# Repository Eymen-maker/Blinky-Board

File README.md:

# Blinky-Board

A blinky board that i made with free-form wiring (aka no pcb, only wire ), but it still has a pcb file to be my reference point.
Small note: pcb has 10 leds but real life build only has 5 as hand wiring 10 leds that close would have been hell.

(there is zero short circuits, i also have no idea how)

[blinky board BOM - Sayfa1.csv](https://github.com/user-attachments/files/30831607/blinky.board.BOM.-.Sayfa1.csv)
Names," links (these are all bought physically, from onur çarşısı / izmir)",Notes

555 timer,https://www.robotistan.com/ne555-dip8,

cd4017,https://robotistanpro.com/lingxingic-cd40175bmlx,

1k ohm resistor,https://www.lcsc.com/product-detail/C2979794.html?spm=wm.fly.bg.7.stp___wm.fly.lb.6.ml&lcsc_vid=Q1ZWUgUDEwUMBgZXRQdcA1ACElBeVFVQQgBZVwZXE1cxVlNeRFJaVldeQFdeUzsOAxUeFF5JWBYZEEoBGA4JCwFIFA4DSA%3D%3D, 

470 ohm resistor,https://www.lcsc.com/product-detail/C1374787.html?spm=wm.fly.bg.13.stp___wm.fly.lb.6.ml&lcsc_vid=Q1ZWUgUDEwUMBgZXRQdcA1ACElBeVFVQQgBZVwZXE1cxVlNeRFJaVldeQFdeUzsOAxUeFF5JWBYZEEoBGA4JCwFIFA4DSA%3D%3D, 

1 uF electrolytic capacitor,https://www.lcsc.com/product-detail/C2927584.html?spm=wm.fly.bg.1.stp___wm.fly.tp.1.ml&lcsc_vid=Q1ZWUgUDEwUMBgZXRQdcA1ACElBeVFVQQgBZVwZXE1cxVlNeRFJaVldeQFdeUzsOAxUeFF5JWBYZEEoBGA4JCwFIFA4DSA%3D%3D, 

0.01 uF capacitor,https://www.lcsc.com/product-detail/C2299493.html?spm=wm.fly.bg.0.xh___wm.fly.tp.3.ml&lcsc_vid=Q1ZWUgUDEwUMBgZXRQdcA1ACElBeVFVQQgBZVwZXE1cxVlNeRFJaVldeQFdeUzsOAxUeFF5JWBYZEEoBGA4JCwFIFA4DSA%3D%3D, 

50k varible resistor,https://www.lcsc.com/product-detail/C5848785.html?spm=wm.fly.bg.3.stp___wm.fly.tp.1.ml&lcsc_vid=Q1ZWUgUDEwUMBgZXRQdcA1ACElBeVFVQQgBZVwZXE1cxVlNeRFJaVldeQFdeUzsOAxUeFF5JWBYZEEoBGA4JCwFIFA4DSA%3D%3D,not the same one but any 50 k ohm vareable resistor woud do

10 leds,literally anywhere,was 20x1 i just cut it

2 male socket pieces,literally anywhere,

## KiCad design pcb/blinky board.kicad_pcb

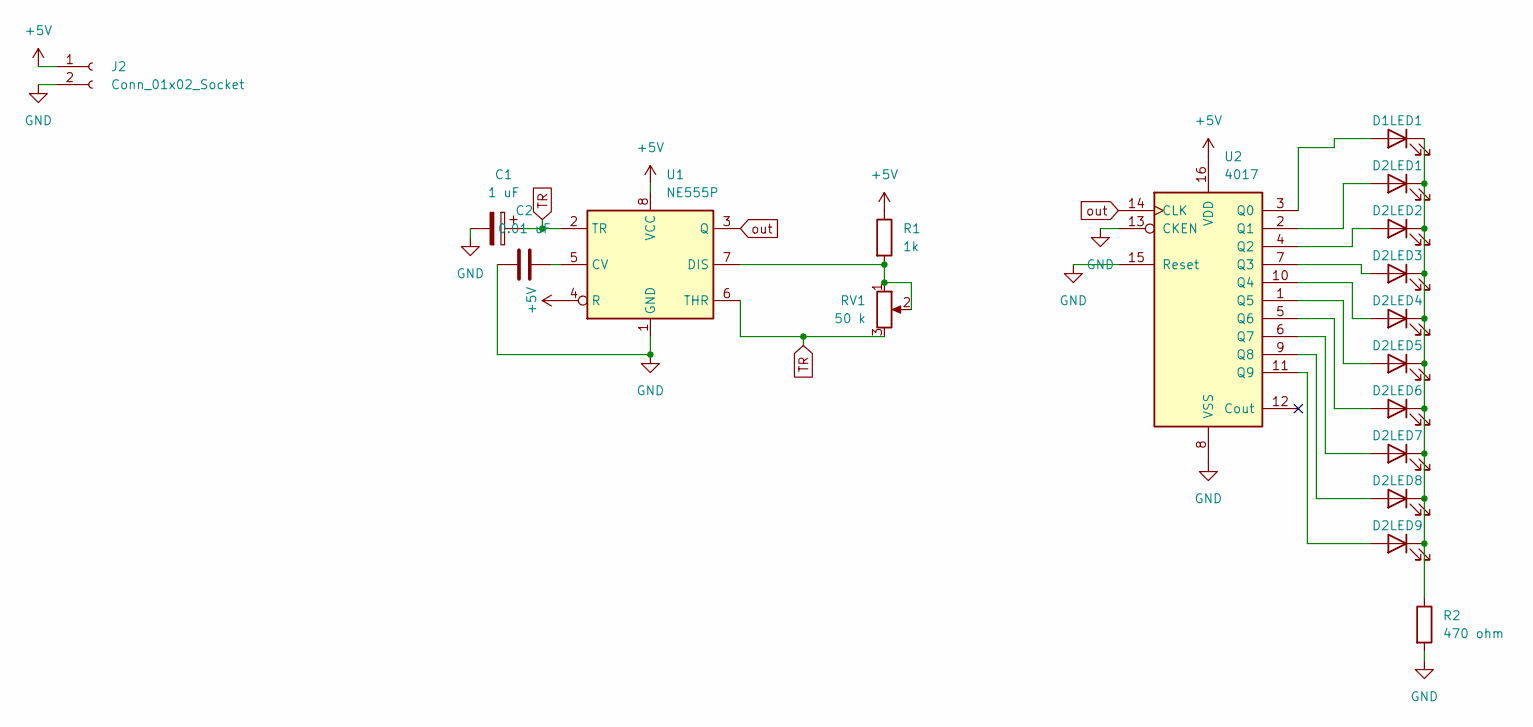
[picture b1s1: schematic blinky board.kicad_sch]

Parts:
C1: 1 uF; CP_Radial_D5.0mm_P2.00mm
C2: 0.01 uF; C_Disc_D7.5mm_W2.5mm_P5.00mm
D1LED1, D2LED1, D2LED2, D2LED3, D2LED4, D2LED5, D2LED6, D2LED7, D2LED8, D2LED9: LED_D3.0mm
J2: Conn_01x02_Socket; PinHeader_1x02_P2.54mm_Vertical
R1: 1k; R_Axial_DIN0207_L6.3mm_D2.5mm_P7.62mm_Horizontal
R2: 470 ohm; R_Axial_DIN0207_L6.3mm_D2.5mm_P7.62mm_Horizontal
RV1: 50 k; Potentiometer_Vishay_T93YA_Vertical
U1: NE555P; DIP-8_W7.62mm
U2: 4017; N16

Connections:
+5V: J2.1, R1.1, U1.4 (R), U1.8 (VCC), U2.16 (VDD)
GND: C1.2, C2.2, J2.2, R2.2, U1.1 (GND), U2.8 (VSS), U2.13 (CKEN), U2.15 (Reset)
unnamed: D1LED1.2 (A), U2.3 (Q0)
unnamed: D1LED1.1 (K), D2LED1.1 (K), D2LED2.1 (K), D2LED3.1 (K), D2LED4.1 (K), D2LED5.1 (K), D2LED6.1 (K), D2LED7.1 (K), D2LED8.1 (K), D2LED9.1 (K), R2.1
unnamed: D2LED1.2 (A), U2.2 (Q1)
unnamed: D2LED2.2 (A), U2.4 (Q2)
unnamed: D2LED3.2 (A), U2.7 (Q3)
unnamed: D2LED4.2 (A), U2.10 (Q4)
unnamed: D2LED5.2 (A), U2.1 (Q5)
unnamed: D2LED6.2 (A), U2.5 (Q6)
unnamed: D2LED7.2 (A), U2.6 (Q7)
unnamed: D2LED8.2 (A), U2.9 (Q8)
unnamed: D2LED9.2 (A), U2.11 (Q9)
unnamed: C2.1, U1.5 (CV)
unnamed: R1.2, RV1.1, RV1.2, U1.7 (DIS)
TR: C1.1, RV1.3, U1.2 (TR), U1.6 (THR)
out: U1.3 (Q), U2.14 (CLK)

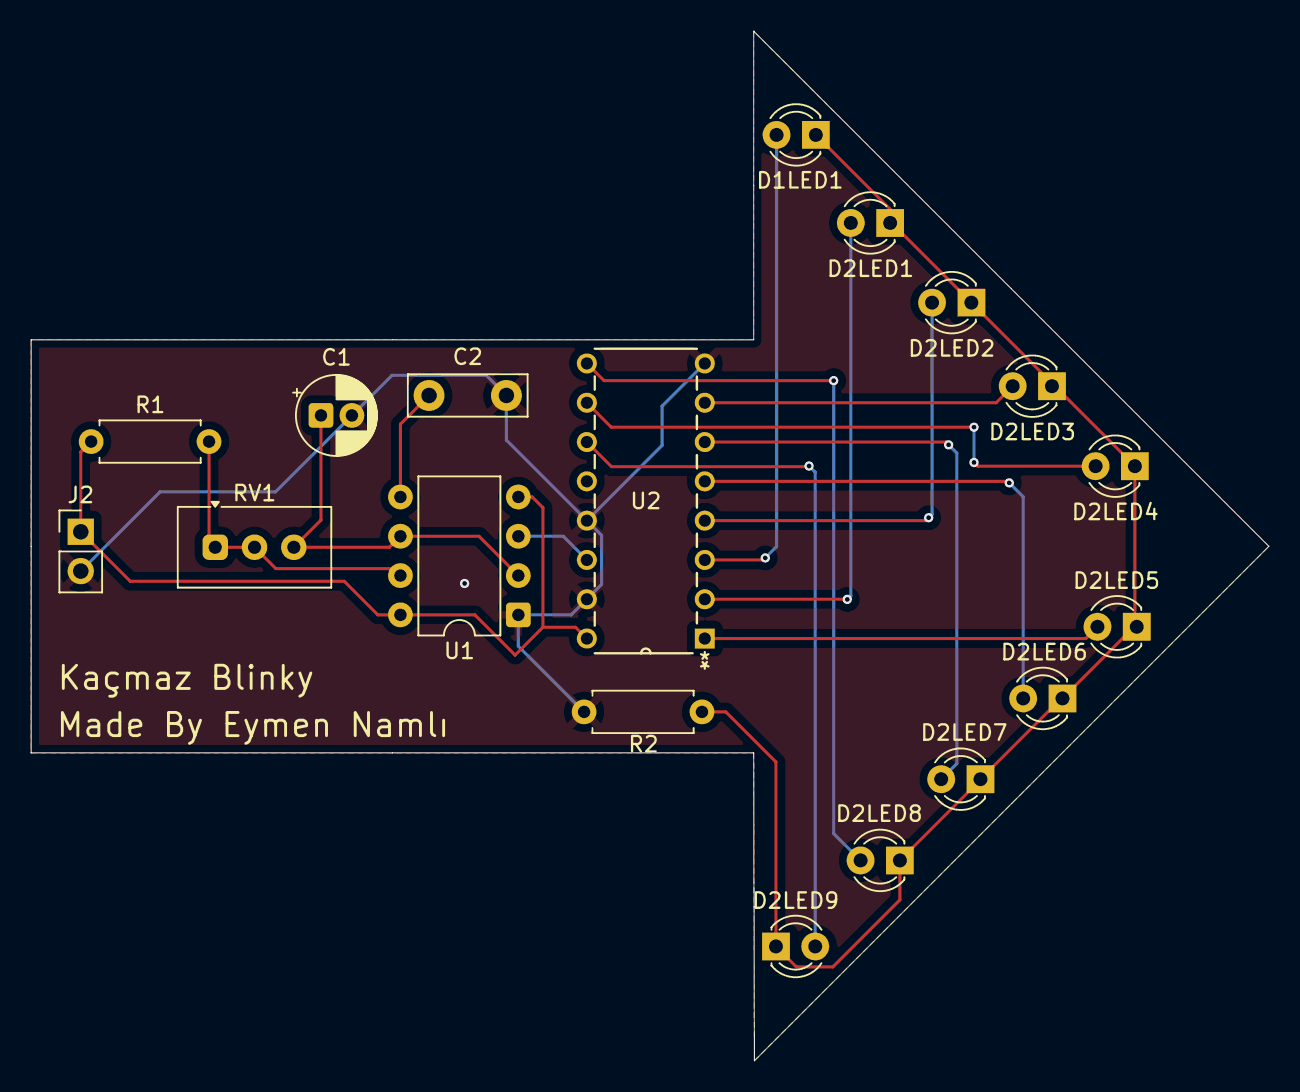
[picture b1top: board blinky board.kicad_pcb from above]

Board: 2 copper layers, 80.0 x 66.6 mm, 18 parts (0 on the bottom side), 17 nets.

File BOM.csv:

Names," links (these are all bought physically, from onur çarşısı / izmir)",Notes
555 timer,https://www.robotistan.com/ne555-dip8,
cd4017,https://robotistanpro.com/lingxingic-cd40175bmlx,
1k ohm resistor,https://www.lcsc.com/product-detail/C2979794.html?spm=wm.fly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, 
470 ohm resistor,https://www.lcsc.com/product-detail/C1374787.html?spm=wm.fly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, 
1 uF electrolytic capacitor,https://www.lcsc.com/product-detail/C2927584.html?spm=wm.fly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, 
0.01 uF capacitor,https://www.lcsc.com/product-detail/C2299493.html?spm=wm.fly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, 
50k varible resistor,https://www.lcsc.com/product-detail/C5848785.html?spm=wm.fly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,not the same one but any 50 k ohm vareable resistor woud do
10 leds,literally anywhere,was 20x1 i just cut it
2 male socket pieces,literally anywhere,
